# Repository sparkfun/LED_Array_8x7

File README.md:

SparkFun LED Array 8x7
======================

[*SparkFun LED Array - 8x7*](https://www.sparkfun.com/products/13795)

56 Charlieplexed LEDs arranged in an 8x7 array. The board requires 8 pins, and the library supports any ATmega 328-based Arduino.

Repository Contents
-------------------

* **/Hardware** - Eagle design files (.brd, .sch)
* **/Libraries** - Libraries for use with the SparkFun LED Array - 8x7
* **/Production** - Production panel files (.brd)

Documentation
--------------
* **[Library](https://github.com/sparkfun/SparkFun_LED_Array_8x7_Arduino_Library)** - Arduino library for the LED Array 8x7.
* **[Hookup Guide](https://learn.sparkfun.com/tutorials/sparkfun-led-array-8x7-hookup-guide)** - Basic hookup guide for the LED Array 8x7.

Product Versions
----------------
* [COM-13795](https://www.sparkfun.com/products/13795)- Basic part and short description here

Version History
---------------
* [v_H1.1_L1.3.1](https://github.com/sparkfun/LED_Array_8x7/tree/v_H1.1_L1.3.1) - Hardware version 1.1, library version 1.3.1. Compatible with Arduino 1.6+
* [v_H1.1_L1.3.0](https://github.com/sparkfun/LED_Array_8x7/tree/v_H1.1_L1.3.0) - Hardware version 1.1, library version 1.3.0. Compatible with Arduino 1.6+

License Information
-------------------

This product is _**open source**_! 

Please review the LICENSE.md file for license information. 

If you have any questions or concerns on licensing, please contact techsupport@sparkfun.com.

Distributed as-is; no warranty is given.

- Your friends at SparkFun.

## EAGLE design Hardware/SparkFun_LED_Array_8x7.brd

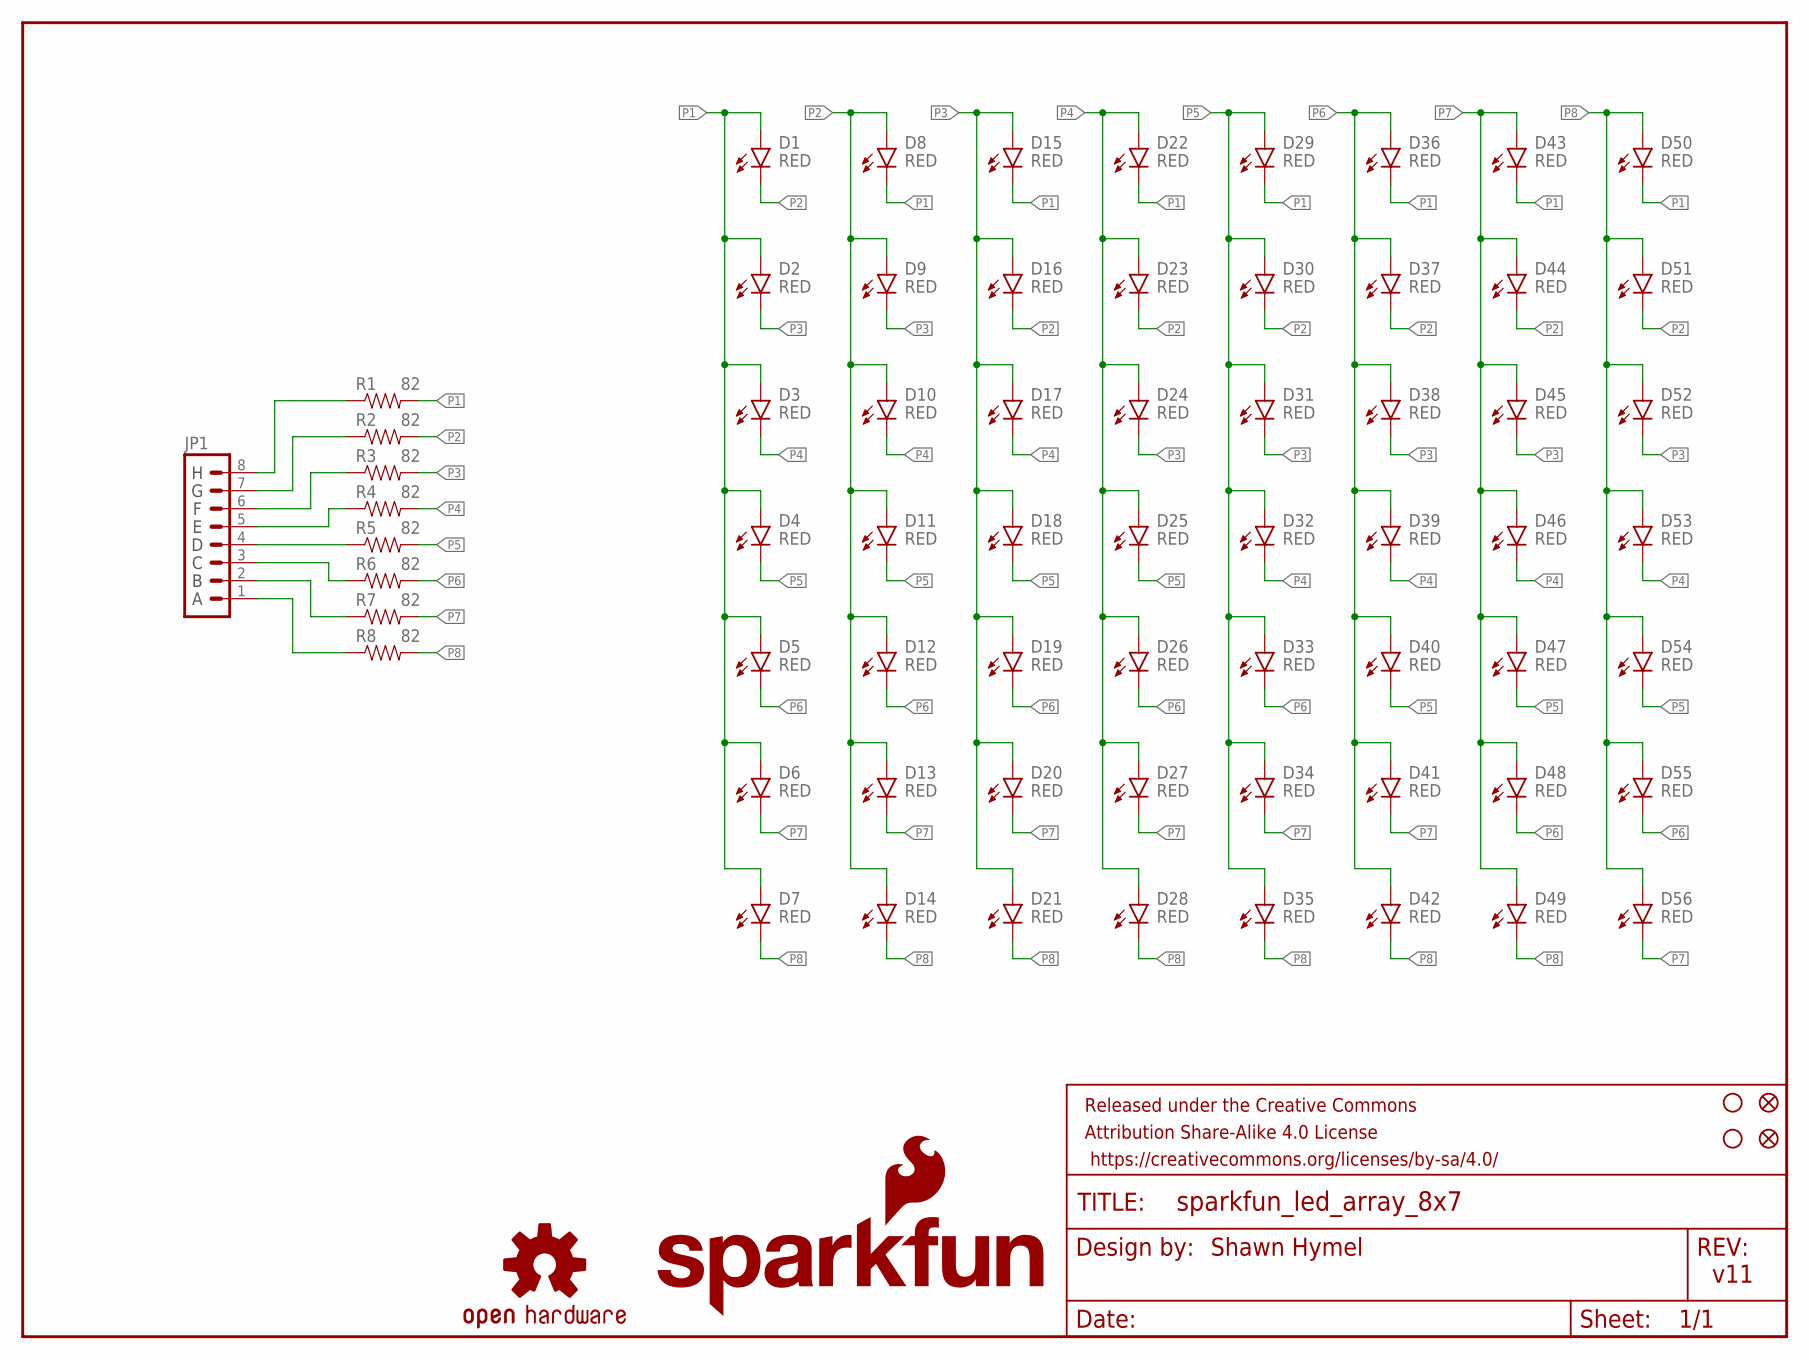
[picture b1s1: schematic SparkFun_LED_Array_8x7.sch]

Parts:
D1, D2, D3, D4, D5, D6, D7, D8, D9, D10, D11, D12, D13, D14, D15, D16, D17, D18, D19, D20, D21, D22, D23, D24, D25, D26, D27, D28, D29, D30, D31, D32, D33, D34, D35, D36, D37, D38, D39, D40, D41, D42, D43, D44, D45, D46, D47, D48, D49, D50, D51, D52, D53, D54, D55, D56: RED; LED-0603
FID1, FID2: FIDUCIAL1X2; FIDUCIAL-1X2
FRAME1: FRAME-LETTER; CREATIVE_COMMONS
JP1: M08LOCK_NO_SILK; 1X08_LOCK_NO_SILK
LOGO2: OSHW-LOGOS; OSHW-LOGO-S
R1, R2, R3, R4, R5, R6, R7, R8: 82; 0603-RES
STANDOFF1, STANDOFF2: STAND-OFF
U$1: SFE_LOGO_NAME_FLAME.1_INCH; SFE_LOGO_NAME_FLAME_.1

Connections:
unnamed: JP1.4, R5.1
unnamed: JP1.5, R4.1
unnamed: JP1.6, R3.1
unnamed: JP1.7, R2.1
unnamed: JP1.8, R1.1
unnamed: JP1.3, R6.1
unnamed: JP1.2, R7.1
unnamed: JP1.1, R8.1
P1: D1.A, D2.A, D3.A, D4.A, D5.A, D6.A, D7.A, D8.C, D15.C, D22.C, D29.C, D36.C, D43.C, D50.C, R1.2
P2: D1.C, D8.A, D9.A, D10.A, D11.A, D12.A, D13.A, D14.A, D16.C, D23.C, D30.C, D37.C, D44.C, D51.C, R2.2
P3: D2.C, D9.C, D15.A, D16.A, D17.A, D18.A, D19.A, D20.A, D21.A, D24.C, D31.C, D38.C, D45.C, D52.C, R3.2
P4: D3.C, D10.C, D17.C, D22.A, D23.A, D24.A, D25.A, D26.A, D27.A, D28.A, D32.C, D39.C, D46.C, D53.C, R4.2
P5: D4.C, D11.C, D18.C, D25.C, D29.A, D30.A, D31.A, D32.A, D33.A, D34.A, D35.A, D40.C, D47.C, D54.C, R5.2
P6: D5.C, D12.C, D19.C, D26.C, D33.C, D36.A, D37.A, D38.A, D39.A, D40.A, D41.A, D42.A, D48.C, D55.C, R6.2
P7: D6.C, D13.C, D20.C, D27.C, D34.C, D41.C, D43.A, D44.A, D45.A, D46.A, D47.A, D48.A, D49.A, D56.C, R7.2
P8: D7.C, D14.C, D21.C, D28.C, D35.C, D42.C, D49.C, D50.A, D51.A, D52.A, D53.A, D54.A, D55.A, D56.A, R8.2

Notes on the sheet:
Shawn Hymel
v11

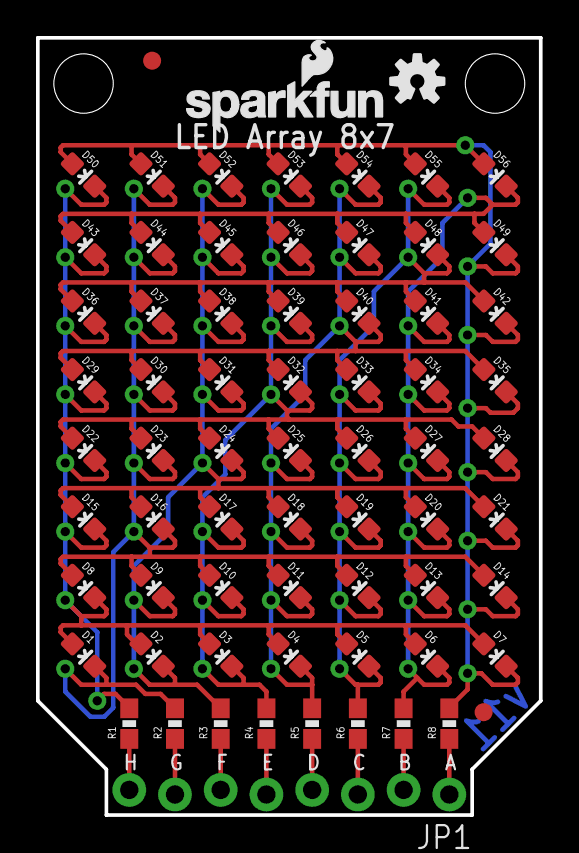
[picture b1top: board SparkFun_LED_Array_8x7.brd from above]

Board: 2 copper layers, 27.9 x 43.2 mm, 72 parts (0 on the bottom side), 16 nets.

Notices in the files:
parts and their libraries:
SparkFun-LED: Licensing: Creative Commons ShareAlike 4.0 International - https://creativecommons.org/licenses/by-sa/4.0
SparkFun-Aesthetics: Released under the Creative Commons Attribution Share-Alike 4.0 License
SparkFun-Aesthetics: https://creativecommons.org/licenses/by-sa/4.0
